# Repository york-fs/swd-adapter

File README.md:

# SWD Programming Adapter

Enables a reliable connection between an **ST-Link clone** and a **1.27 mm 2×3 pin IDC connector**.  
Power output can be configured for **3.3 V** or **5 V** (default: **5 V**).  
Includes a **red status LED** to indicate power.

## Usage

- Connect the adapter to the ST-Link clone **with the board facing upward**.  
- Select the desired power level using the **solder bridge**:  
  - **5 V** is connected by default.  
  - To switch to **3.3 V**, **cut the 5 V bridge** and **solder the 3.3 V bridge** instead.  
- **Verify your ST-Link clone’s pinout** before making any connections.

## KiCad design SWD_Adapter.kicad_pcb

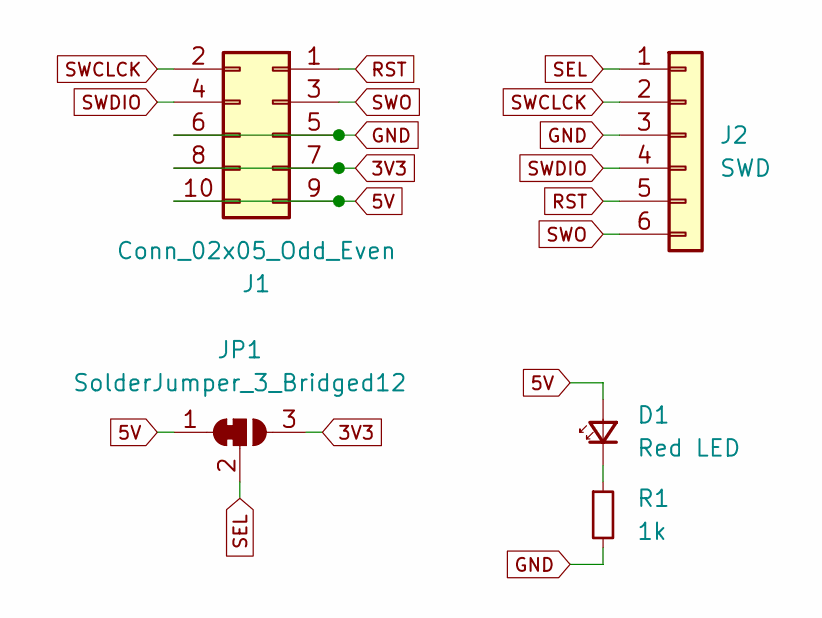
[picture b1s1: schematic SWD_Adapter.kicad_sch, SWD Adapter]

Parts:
D1: Red LED; LED_0603_1608Metric; Mfr # NCD0603R1
J1: Conn_02x05_Odd_Even; PinSocket_2x05_P2.54mm_Vertical; Mfr # ZX-PM2.54-2-5PWS
J2: SWD; IDC-Connector-2x3; Mfr # HX JN1.27-2x3P ZZ H4.9
JP1: SolderJumper_3_Bridged12; SolderJumper-3_P1.3mm_Bridged12_RoundedPad1.0x1.5mm
R1: 1k; R_0603_1608Metric; Mfr # 0603WAF1001T5E

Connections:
3V3: J1.7, J1.8, JP1.3 (B)
5V: D1.2 (A), J1.9, J1.10, JP1.1 (A)
GND: J1.5, J1.6, J2.3, R1.2
unnamed: D1.1 (K), R1.1
RST: J1.1, J2.5
SEL: J2.1, JP1.2 (C)
SWCLCK: J1.2, J2.2
SWDIO: J1.4, J2.4
SWO: J1.3, J2.6

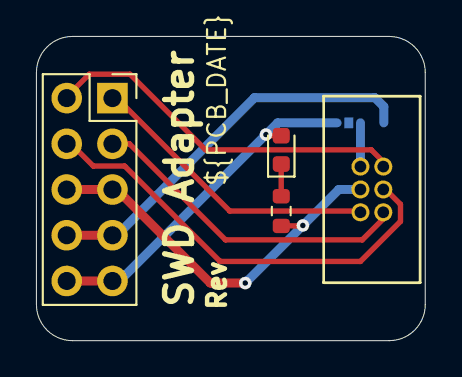
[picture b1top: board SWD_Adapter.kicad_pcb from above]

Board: 2 copper layers, 21.6 x 16.9 mm, 5 parts (1 on the bottom side), 9 nets.

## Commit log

2025-10-12 Fixed formatting
2025-10-26 meta: Add .lck files to gitignore
2025-10-26 kicad-library: Update to latest version
2025-10-26 project: Link to footprint library
2025-10-26 meta: Add .gitattributes
2025-10-26 schematic: Fix DRC warning
2025-10-26 bom: Fill in BOM info
2025-10-26 ci: Add CI
2025-11-22 meta: Update gitignore
2025-11-22 meta: Set LF line endings explicitly
